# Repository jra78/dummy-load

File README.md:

# dummy-load
Dummy load about 100mA to 3A maks 40W

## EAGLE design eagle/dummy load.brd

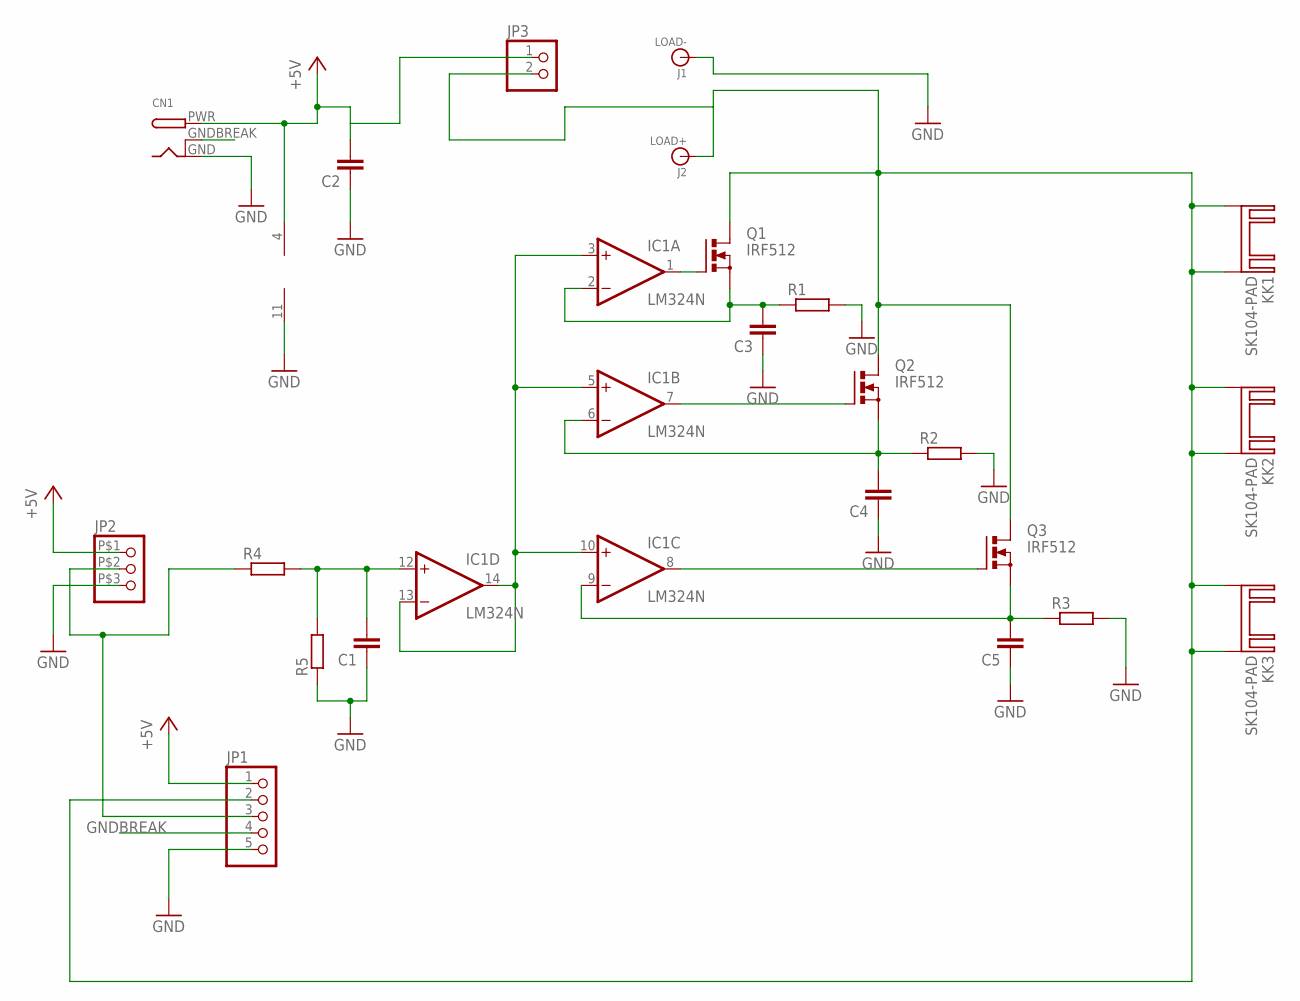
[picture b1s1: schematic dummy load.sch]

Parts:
C1, C2, C3, C4, C5: C-EUC0805; C0805
CN1: DCBARRELPTH; DCJACK_2MM_PTH
IC1: LM324N; DIL14
J1: LOAD-; BANANA_CONN
J2: LOAD+; BANANA_CONN
JP1: PINHD-1X5/90; 1X05/90
JP2: PINHD-1X35.08; 1X03/5.08
JP3: PINHD-1X2; 1X02
KK1, KK2, KK3: SK104-PAD
Q1, Q2, Q3: IRF512; TO220BV
R1, R2, R3: R-EU_VTA52; VTA52
R4, R5: R-EU_R0805; R0805

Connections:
+5V: C2.2, CN1.PWR, IC1.4 (V+), JP1.1, JP2.P$1 (1), JP3.1
GND: C1.1, C2.1, C3.1, C4.1, C5.1, CN1.GND, IC1.11 (V-), J1.P$1, JP1.5, JP2.P$3 (3), R1.2, R2.2, R3.2, R5.1
GNDBREAK: CN1.GNDBREAK, JP1.4
LOAD+: J2.P$1, JP1.2, JP3.2, KK1.K1, KK1.K2, KK2.K1, KK2.K2, KK3.K1, KK3.K2, Q1.D, Q2.D, Q3.D
unnamed: IC1.1 (OUT), Q1.G
unnamed: IC1.7 (OUT), Q2.G
unnamed: IC1.8 (OUT), Q3.G
unnamed: C3.2, IC1.2 (-IN), Q1.S, R1.1
unnamed: C4.2, IC1.6 (-IN), Q2.S, R2.1
unnamed: C5.2, IC1.9 (-IN), Q3.S, R3.1
unnamed: JP1.3, JP2.P$2 (2), R4.1
unnamed: IC1.3 (+IN), IC1.5 (+IN), IC1.10 (+IN), IC1.13 (-IN), IC1.14 (OUT)
unnamed: C1.2, IC1.12 (+IN), R4.2, R5.2

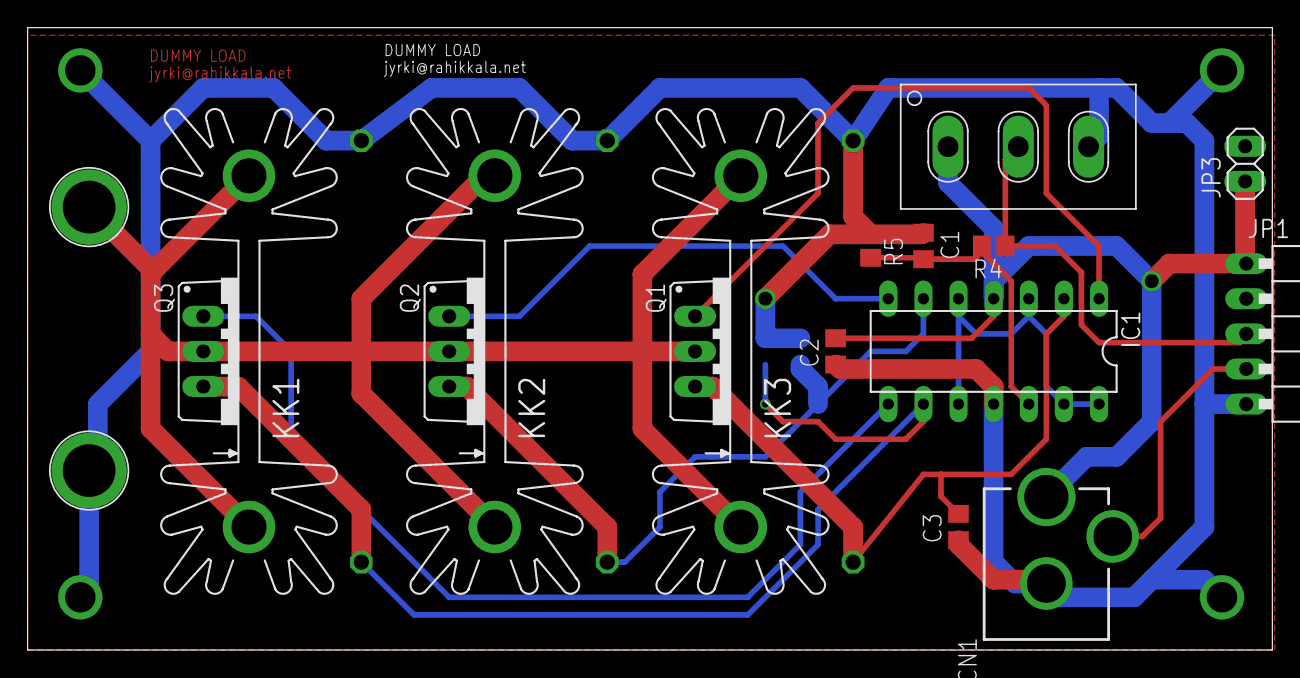
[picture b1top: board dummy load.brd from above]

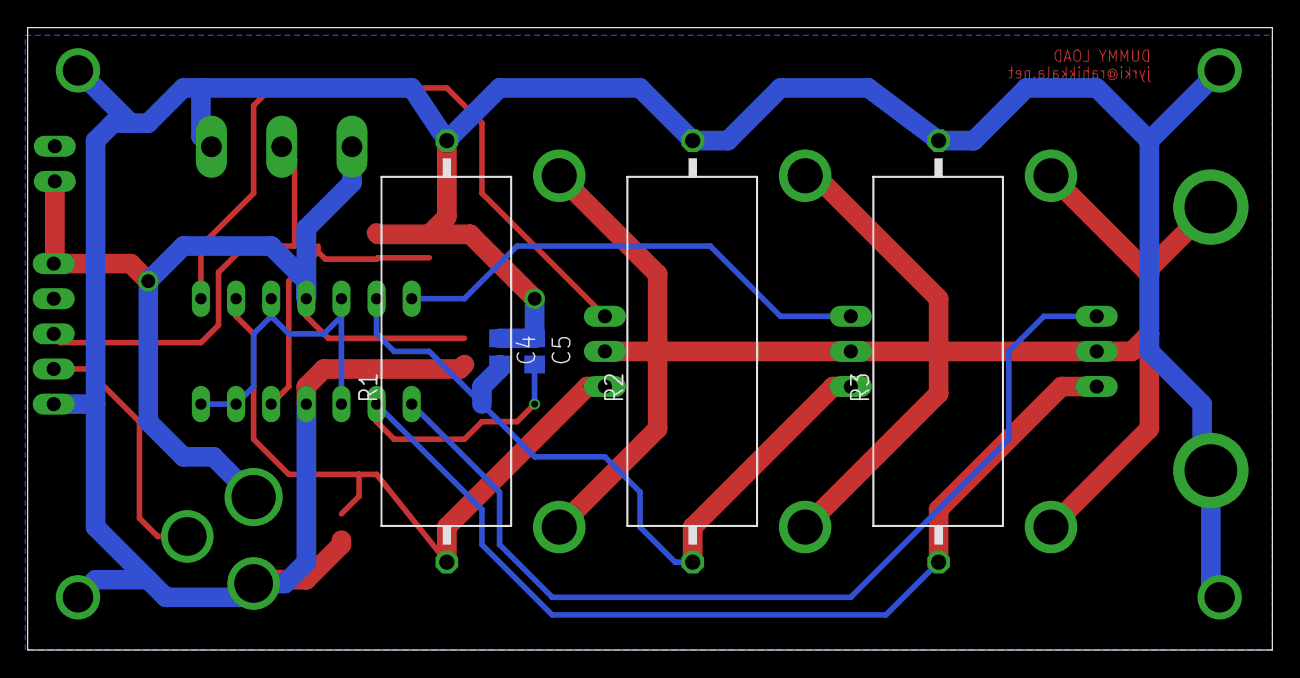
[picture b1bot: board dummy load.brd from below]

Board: 2 copper layers, 90.0 x 45.0 mm, 23 parts (5 on the bottom side), 13 nets.

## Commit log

2015-08-07 Added EAGLE files.

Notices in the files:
parts and their libraries:
SparkFun-Connectors: Licensing: Creative Commons ShareAlike 4.0 International - https://creativecommons.org/licenses/by-sa/4.0
